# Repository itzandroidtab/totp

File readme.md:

## Hardware TOTP token
Open source hardware TOTP token. Currently targets the LPC1756, LPC1758 and LPC1759 (with a small change it should also run on the LPC1754). 

### Features
* keys never leave the token after setup
* support for 6 and 8 digit tokens
* enter button types 6/8 digit token using HID keyboard (any device that supports HID keyboards should work)
* supports up to 32 profiles
* rechargable RTC battery
* USB mode to add/delete profiles using a CSV file (supports base32, hex and hex string)
* support to change the RTC calibration values in the settings
* support for setting the time + timezone (currently only GMT)
* 60 seconds screen timeout
* support for different intervals (supports 1 - 180 seconds)

### Images
Images can be found in the project logs at [hackaday](https://hackaday.io/project/194867-hardware-2fa-totp-authenticator)

### TODO
* encrypt profiles
* add support for more than 32 profiles (needs a rework if more profiles are required. The profiles are copied to ram and there is not enough for more at the moment. If we leave them in flash we can store a lot more)
* rework the calibration and time settings screens

### Compiling
TOTP uses [klib](https://github.com/itzandroidtab/klib). This repo can be cloned in the klib project folder. See [build.yml](./.github/workflows/build.yml) for more info on compiling this project.

### Extra
Is intended to be used with [USB dfu bootloader](https://github.com/itzandroidtab/dfu_bootloader). To build without bootloader support remove the `+ 8k` and `- 8k` from line 20 in the `linkerscript.ld` of this project.

The LPC1756 does not have enough ram to hold a full framebuffer (240 * 135 * 2 = 64'800 bytes). To work around this issue, we use 2 smaller framebuffers we alternate between. While one framebuffer is being transferred to the screen using DMA we fill the other.

To make it easier (for me) the whole screen is written to this smaller framebuffer. The pixels that do not fit the framebuffer are thrown away. This does waste CPU cycles but is not limiting the framerate. Filling a full frame with pixels takes around 6 milliseconds. Writing a full frame of framebuffers to the display takes around 11 milliseconds. This limits the maximum framerate to ≈ 85FPS. To get a consistant frame rate there is a limit of 60FPS.

The main screen takes the longest to draw. This is caused by the amount of pixels of the circle it needs to draw. The circle is generated on compile time to work around that the LPC175x family does not have a FPU. These generated pixels use 8640 bytes of flash.

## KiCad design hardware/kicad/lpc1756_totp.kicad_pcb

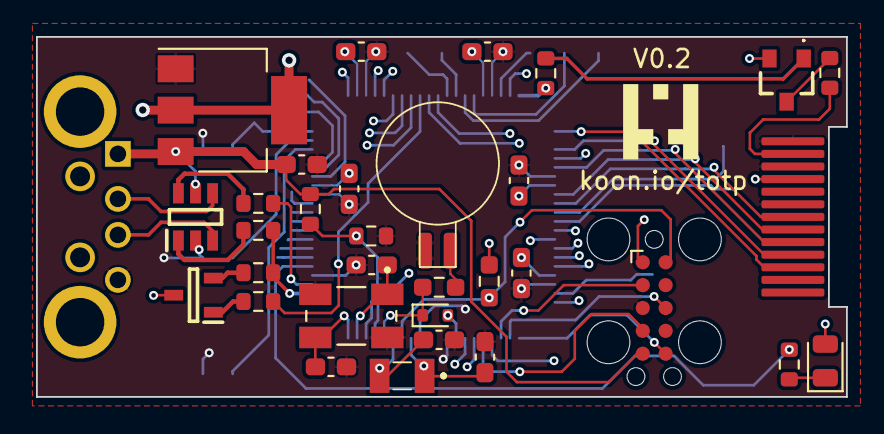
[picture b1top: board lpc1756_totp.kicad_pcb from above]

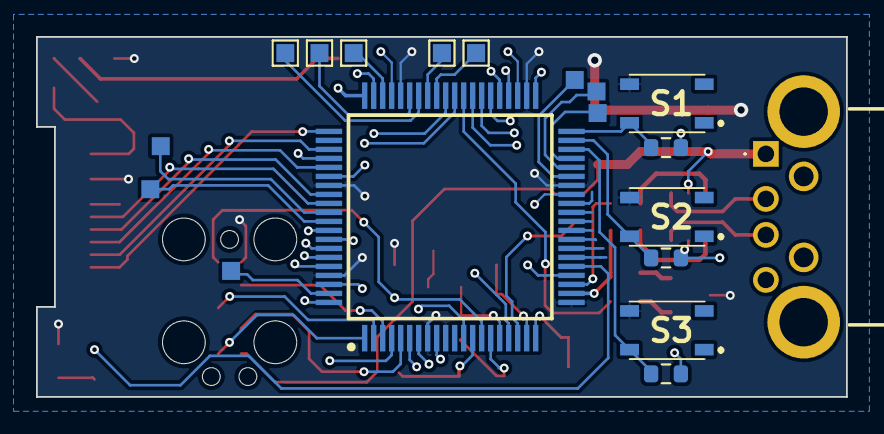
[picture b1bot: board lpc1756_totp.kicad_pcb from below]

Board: 2 copper layers, 45.0 x 20.0 mm, 40 parts (8 on the bottom side), 38 nets.

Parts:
BT1: MS621FE-FL11E
C1, C2: 10uF; C_0603_1608Metric_Pad1.08x0.95mm_HandSolder
C3, C4, C5, C6: 18pF; C_0603_1608Metric_Pad1.08x0.95mm_HandSolder
C7, C8, C9, C10: 100nF; C_0603_1608Metric_Pad1.08x0.95mm_HandSolder
D1: IP4234CZ6,125; SOP95P275X110-6N
D2: LED; LED_0805_2012Metric
D3: D_Schottky; D_SOD-523
IC1: LPC1756FBD80,551; QFP50P1400X1400X160-80N
J1: MC32603
Q1: BC856A,215; SOT95P230X110-3N
Q2: RN2425_TE85L,F_; RN2425TE85LF
R1, R2: 33; R_0603_1608Metric
R3, R6: 300; R_0603_1608Metric
R4: 750; R_0603_1608Metric
R5: 1000; R_0603_1608Metric
R7: 1K; R_0603_1608Metric
R8: 1.5K; R_0603_1608Metric
R9, R11, R13, R14: 1k; R_0603_1608Metric
R10: 10K; R_0603_1608Metric_Pad0.98x0.95mm_HandSolder
R12: 1.8K; R_0603_1608Metric_Pad0.98x0.95mm_HandSolder
S1, S2, S3: PTS810SJK250SMTRLFS; PTS810SJG250SMTRLFS
U1: st7735_mini_lcd; ST7735
U2: AMS1117-3.3; SOT-223-3_TabPin2
U3: TC2050; Tag-Connect_TC2050-IDC-FP_2x05_P1.27mm_Vertical
Y1: ABS07-32.768KHZ-T; ABS0716632768KHZT
Y2: ABM3B-12.000MHZ-B2-T; XTAL_ABM3B-12.000MHZ-B2-T

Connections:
+3.3V: C2.1, C7.1, C8.1, C9.1, C10.1, D2.2 (A), D3.2 (A), IC1.8 (VDDA), IC1.10 (VREFP), IC1.21 (VDD(3V3)_1), IC1.34 (VDD(REG)(3V3)_1), IC1.42 (VDD(3V3)_2), IC1.56 (VDD(3V3)_3), IC1.67 (VDD(REG)(3V3)_2), IC1.77 (VDD(3V3)_4), Q1.3, Q2.2, R10.1, S1.4, S2.4, S3.4, U1.10 (VDD), U2.2 (VO), U3.1 (VTref)
+5V: C1.1, D1.5 (VCC), J1.1, R4.1, U2.3 (VI), U3.5 (5V-Supply)
/CPU/RSTN: IC1.14 (~RESET), R10.2, U3.10 (nReset)
/CPU/XTAL_RTC_X1: C3.1, IC1.13 (RTCX1), Y1.1
/CPU/XTAL_RTC_X2: C4.1, IC1.15 (RTCX2), Y1.2
/CPU/XTAL_X1: C5.1, IC1.19 (XTAL1), Y2.1
/CPU/XTAL_X2: C6.1, IC1.20 (XTAL2), Y2.3
/USB/USB_D+: D1.3 (ESD_I/O_CH_1_2), J1.3
/USB/USB_D-: D1.4 (ESD_I/O_CH_2_1), J1.2
/User/LCD_B: Q2.3, R6.2
D+: IC1.22 (P0[29]/USB_D+), R2.2, R8.1
D-: IC1.23 (P0[30]/USB_D-), R1.2
GND: BT1.2 (-), C1.2, C2.2, C3.2, C4.2, C5.2, C6.2, C7.2, C8.2, C9.2, C10.2, D1.2 (VDD), IC1.9 (VSSA), IC1.12 (VREFN), IC1.24 (VSS_1), IC1.33 (VSS_2), IC1.43 (VSS_3), IC1.57 (VSS_4), IC1.66 (VSS_5), IC1.78 (VSS_6), J1.4, R5.2, R11.1, R13.1, R14.1, U1.8 (GND), U1.11 (LEDK), U1.13 (GND), U2.1 (GND), U3.3 (GND), Y2.2 (GND), Y2.4 (GND)
LCD_BLK: IC1.60 (P2[0]/PWM1[1]/_TXD1), R9.2
LCD_CS: IC1.69 (P1[15]/_ENET_REF_CLK), U1.7 (CS)
LCD_DC: IC1.65 (P4[28]/RX_MCLK/_MAT2[0]/TXD3), U1.5 (DC)
LCD_MOSI: IC1.61 (P0[9]/I2STX_SDA/_MOSI1/MAT2[3]), U1.3 (MOSI)
LCD_RST: IC1.68 (P4[29]/TX_MCLK/_MAT2[1]/RXD3), U1.6 (RST)
LCD_SCK: IC1.63 (P0[7]/I2STX_CLK/_SCK1/MAT2[1]), U1.4 (SCK)
unnamed: BT1.1 (+), R12.2
unnamed: D1.1 (ESD_I/O_CH_1_1), R2.1
unnamed: D1.6 (ESD_I/O_CH_2_2), R1.1
unnamed: D2.1 (K), R3.2
unnamed: Q1.1, R7.1
unnamed: Q1.2, R8.2
unnamed: Q2.1, R9.1
unnamed: R6.1, U1.12 (LEDA)
TCK: IC1.5 (TCK/SWDCLK), U3.4 (TCK)
TDI: IC1.2 (TDI), U3.8 (TDI)
TDO: IC1.1 (TDO/SWO), U3.6 (TDO)
TMS: IC1.3 (TMS/SWDIO), U3.2 (TMS)
USB_ACT: IC1.25 (P1[18]/_USB_UP_LED/_PWM1[1]/_CAP1[0]), R3.1
USB_CONNECT: IC1.49 (P2[9]/_USB_CONNECT/_RXD2), R7.2
USER_IO0: IC1.40 (P0[11]/RXD2/_SCL2/MAT3[1]), R11.2, S1.2
USER_IO1: IC1.39 (P0[10]/TXD2/_SDA2/MAT3[0]), R13.2, S2.2
USER_IO2: IC1.38 (P0[1]/TD1/RXD3/_SCL1), R14.2, S3.2
VBAT: D3.1 (K), IC1.16 (VBAT), R12.1
VBUS: IC1.18 (P1[30]/VBUS/_AD0[4]), R4.2, R5.1

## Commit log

2024-01-14 initial commit. Added working implementation of a totp hardware dongle.
2024-01-25 added mouse jiggler and cleanup totp
2024-01-25 bugfix incorrect month selection
2024-01-26 bugfix big config files
2024-02-07 updated to new fonts + gui string
2024-02-16 added a 60 seconds screen timeout
2024-02-16 added a readme and pictures
2024-02-16 updated images readme
2024-02-16 html fix
2024-02-16 added newlines before pictures
2024-02-16 added github actions + readme update
2024-02-16 changed github action build type to release
2024-02-16 updated linkerscript to show correct sizes + added profiles location (for lpc1756)
2024-02-16 added STL files for the case
2024-02-16 added kicad files
2024-02-25 added support for GMT timezones
2024-02-25 cleanup font
2024-02-25 added a version option in the settings
2024-02-25 bugfix numbers going out of box
2024-02-25 changed cal options to have text fields instead of 0 and 1 + bugfix going to previous screen
2024-02-25 added option to keep pressing in the numeric popup
2024-02-25 increased version to 0.2
2024-03-06 added support for 8 digit tokens
2024-03-06 made storage load from profile section instead of hardcoded
2024-03-06 cleanup old hardcoded values
2024-03-06 added start of base32 decoding support in the csv file
2024-03-07 added support for base32 decoding in the csv file (#3)
2024-03-07 Added note for profiles in linkerscript
2024-03-07 Storage rework to load from linkerscript (#1)
    * made storage load from profile section instead of hardcoded
    * cleanup old hardcoded values
    * Added note for profiles in linkerscript
2024-03-07 added support for 8 digit tokens (#2)
2024-03-07 bugfix allowing 0 in day field
2024-03-07 changed to version 0.3
2024-03-09 Added link to hackaday and removed images
2024-03-09 removed all images
2024-03-23 changed pi to double
2024-03-23 cleanup unused variables
2024-03-23 changed profile text location to center
2024-03-23 added support for variable intervals
2024-03-24 moved framebuffer to seperate section
2024-03-24 bugfix current out of range when deleting entries
2024-03-24 added messages when manipulating CSV file
2024-03-24 bugfix time not updating straight away when interval is different
2024-03-24 bugfix circle only updating on the second mark + made circle less jittery
2024-03-24 added a error screen if a hardfault occurs
2024-03-24 added LTO in cmakelists
2024-03-24 changed github actions to build on every branch
2024-03-24 bugfix rtc time updating last runtime when the interval changed
2024-03-24 bugfix showing old messages when entering config
2024-03-27 cleanup entries
2024-03-27 added profile index to main screen
2024-03-28 bugfix not clearing framebuffer on all screens
2024-03-28 reworked menu for better settings screen
2024-03-29 bugfix going out of bounds in the menu
2024-03-29 added build folder to gitignore
2024-03-30 changed to new chip folder for startup
2024-03-30 changed github actions to chip folder
2024-05-27 made it remember the last selected profile
2024-05-27 splitted timezone from time to allow changing the timezone without changing the time
2024-08-11 Changed instructions to build without bootloader support
2024-08-31 changed lookuptable type to uint8_t
2025-01-26 Updated DMA template parameter to std::endian
2025-02-20 Updated dependencies github actions
2025-02-20 Updated upload artifacts to v4
2026-06-02 Updated project to work with latest klib
2026-06-10 Updated klib to latest version
